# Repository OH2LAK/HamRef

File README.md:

# HamREF

A small GNSS-disciplined 10 MHz frequency reference and precision time server for the amateur radio shack — built around the u-blox LEA-M8S GNSS module.

> **Status: early architecture / pre-prototype.** Proto-1 schematic and PCB (v0.1) are generated and routed, not yet built or tested; a firmware proof of concept (PIO counter + disciplining loop, host-simulated, not yet run on hardware) is in [`firmware/`](firmware/). This README documents the design as currently planned so the repo has a real starting point; sections below are marked `TODO` where work hasn't started.

<p align="center">
  <br>
  <em>Proto-1 bring-up board (v0.1): 4-layer, 100 × 80 mm (fits the Fischer AKG 105.26 case grooves), 3D view from KiCad. Design files in <a href="hardware/proto-v0.1/"><code>hardware/proto-v0.1/</code></a>.</em>
</p>

The proto-1 board has four coaxial connectors along the rear edge: **SMA** (GNSS antenna input), **BNC REF OUT** (10 MHz from the OCXO), **BNC 1PPS OUT** and **BNC AUX OUT**. AUX OUT outputs a programmable frequency (3.3 V CMOS) generated by the Si5351C synthesizer, which is clocked from the OCXO, so it is locked to the same reference as the 10 MHz output.

## What this is

HamREF provides two things a well-equipped station needs and usually has to buy separately:

- A **10 MHz reference output** (BNC, 50 Ω) to lock transceivers, synthesizers, and test equipment, plus a **programmable AUX output** for other frequencies (e.g. 25 MHz, 27 MHz for satellite LNBs, 40 MHz for a Pluto SDR, or an arbitrary frequency).
- A **1 PPS timing output** which can be used to lock and synck devices to the world-standard one pulse per second.
- A **precision time source for the shack computer**, disciplined by GNSS, accurate enough for FT8 and other digital modes.

Status (GNSS lock, satellite count, PPS accuracy, OCXO discipline state) is shown on a small monochrome OLED plus two multicolor status LEDs (GPSDO / NTP) on the front panel — color and blink/steady pattern indicate different states. A front-panel rotary encoder drives the menu; full parameter configuration is also available over USB (see [Enclosure](#enclosure) below).

## Why not just use the GNSS module's own 10 MHz output?

The LEA-M8S can output a configurable timepulse from 0.25 Hz to 10 MHz directly, but that signal is a digitally synthesized pulse train (derived from the module's internal TCXO + fractional-N synthesizer), not a clean analog oscillator. At 10 MHz its jitter (the module's spec is 30 ns RMS / 60 ns 99% at 1 Hz) is significant relative to the 100 ns period, it can show small phase steps at each second boundary, and it provides no holdover if GNSS lock is lost.

HamREF instead uses the classic GPSDO approach: the LEA-M8S's single TIMEPULSE output is configured as **1PPS**, and that one pulse-per-second reference is used by the MCU to discipline a separate free-running OCXO via a DAC-driven EFC loop with a long time constant. The 10 MHz output comes from the OCXO itself — far lower phase noise, plus holdover if satellite lock drops. The same 1PPS/NMEA data feeds the time service to the host computer.

Full rationale and the architecture decision log: [`docs/architecture-and-plan.md`](docs/architecture-and-plan.md) (in Finnish).

## Enclosure

**Fischer Elektronik AKG 105.26** (part AKG1052680ME) — an extruded aluminum mini case for 100 mm eurocards, 105 × 100.3 × 26 mm, natural anodized, with integrated cooling-fin channels. Front and rear panels are separate 2 mm cover plates.

The 26 mm case height (≈22 mm usable panel height) ruled out the originally planned 240x240 color TFT. An EC11-class rotary encoder does fit, though (body ≈11.7×12–13×4.5–8.5 mm, ø7 mm panel bushing — verified against the Farnell EC11 datasheet), so the front panel keeps a physical control after all:

| Panel | Contents |
|---|---|
| Front | 0.91" 128x32 OLED (status), 2 multicolor LEDs (GPSDO, NTP), rotary encoder (menu/control) |
| Rear | SMA (GNSS antenna), BNC (1PPS OUT), BNC (REF OUT 10 MHz), BNC (AUX OUT, programmable), USB-C (host + 5V power) |

The 22 mm limit also constrains component height on the PCB (OCXO included) — still an open item, see the architecture doc.

## Architecture overview

<p align="center">
  <br>
  <em>Block diagram (editable source: <a href="docs/images/HamREF-architecture.svg"><code>HamREF-architecture.svg</code></a>).</em>
</p>

The GNSS module's 1PPS (TIMEPULSE) disciplines the OCXO through the MCU: the RP2350 measures the 10 MHz against the PPS with PIO and steers the EFC through the DAC. REF OUT (10 MHz) comes from the OCXO itself, 1PPS OUT from the GNSS TIMEPULSE, and AUX OUT is a programmable output (Si5351C clocked from the OCXO).

**What is the USB-C port, in plain words?** It is a normal USB-C connector (USB 2.0 only, no Power Delivery, so always 5 V) wired straight to the RP2350's own USB controller. One cable does two jobs: it powers the whole device and it carries data. The data side is a **virtual serial port over USB** (class CDC-ACM): the computer sees an ordinary serial port (`COMx` on Windows, `/dev/ttyACM0` on Linux, `/dev/cu.usbmodem…` on macOS) and needs no special driver. Over that port the device sends the GNSS text sentences and PPS timing data to a small helper program on the computer, which feeds chrony; the computer can also send configuration commands back.

| Acronym | Meaning |
|---|---|
| GNSS | Global Navigation Satellite System: GPS, Galileo, GLONASS, BeiDou |
| 1PPS / PPS | One Pulse Per Second: a pulse aligned to the start of each UTC second |
| TIMEPULSE | u-blox name for the LEA-M8S's programmable timing-pulse output (here set to 1PPS) |
| UART | Universal Asynchronous Receiver/Transmitter: the simple serial link between LEA-M8S and RP2350 |
| NMEA | Text sentences (`$GPGGA`, `$GPRMC` …) in which GNSS receivers report time, position and satellites |
| UBX | u-blox's own binary protocol, used to configure the LEA-M8S |
| USB VBUS | The 5 V power line of a USB cable |
| CDC-ACM | USB Communications Device Class, Abstract Control Model: the standard way to make a USB device look like a serial port |
| PD | USB Power Delivery: negotiation of voltages above 5 V (not used here) |
| I2C | Two-wire bus used for the OLED, the DAC and the Si5351C |
| GPIO | General-purpose input/output pin (drives the status LEDs, reads the encoder) |
| PIO | Programmable I/O: the RP2350's small hardware state machines that count the 10 MHz and timestamp the PPS without CPU jitter |
| Si5351C | Silicon Labs programmable clock generator (I2C); makes the AUX OUT frequency from the OCXO reference |
| OCXO | Oven-Controlled Crystal Oscillator: a crystal kept at constant temperature, the source of the 10 MHz |
| EFC | Electronic Frequency Control: the analog voltage input that fine-tunes the OCXO's frequency |
| DAC | Digital-to-Analog Converter: turns the MCU's number into the EFC voltage |
| SHM | Shared Memory: one of chrony's reference-clock interfaces, where the host helper hands over the timestamps |
| chrony | The time-sync daemon on Linux/macOS that disciplines the computer's clock (an NTP implementation) |
| NTP | Network Time Protocol |

Key hardware decisions so far:

| Item | Decision | Notes |
|---|---|---|
| GNSS module | u-blox LEA-M8S | Fixed — parts already on hand. Footprint and pinout are shared with LEA-M8T. |
| Antenna | Active, external | Antenna supervisor + R_BIAS per u-blox HIM. |
| MCU | RP2350A on a ready-made Raspberry Pi Pico 2 board | Ready-made board keeps HamREF easy to build as a kit. PIO blocks give deterministic 10 MHz counting and 1PPS timestamping without WiFi interrupt jitter; native USB (TinyUSB); UF2 firmware updates. No WiFi in v1. Raspberry Pi Pico 2 (micro-USB) remains a fallback. |
| Oscillator | 5 V OCXO, analog EFC (CTI OSC5A2B02 selected for the prototype) | e.g. Trimble 65256 / IsoTemp 143-141 / CTI OC5SVC25 / Bliley NV47M1008 class part — physical height inside the 22 mm case is still open, see architecture doc. |
| Enclosure | Fischer Elektronik AKG 105.26 (AKG1052680ME) | 105 × 100.3 × 26 mm extruded aluminum, 100 mm eurocard. |
| Display | 0.91" 128x32 mono OLED, I2C | SSD1306-class, 38 × 12 mm PCB (active area 22.4 × 5.6 mm) — fits the 22 mm panel height with margin; 0.96" 128x64 modules do not. |
| Front panel | OLED + 2 multicolor LEDs (GPSDO, NTP) + rotary encoder | EC11-class encoder confirmed to fit the 22 mm panel height. LED color/blink pattern encodes state (firmware TBD). |
| Rear panel | SMA (GNSS antenna), BNC (1PPS OUT), BNC (REF OUT 10 MHz), BNC (AUX OUT, programmable), USB-C (host + 5V power) | All connectors on the back; layout across the 105 mm width still to be confirmed at PCB stage. |
| Power + host link | USB-C | Powers the device (5V); CDC-ACM carries PPS/NMEA to a host-side helper feeding chrony (SHM/PPS refclock), and doubles as the configuration interface alongside the encoder/OLED menu. |

See the architecture doc for the full reasoning, open questions, and the phased project plan.

## Status / roadmap

- [x] Requirements and architecture defined
- [x] Enclosure selected (Fischer AKG 105.26) and display/panel layout locked to it
- [x] MCU selected (RP2350 / Pico 2)
- [ ] Proto-PCB v0.1 (bring-up board, see architecture doc)
- [ ] Breadboard proof of concept (PIO PPS capture + frequency counting, disciplining loop, USB time delivery)
- [ ] KiCad schematic
- [ ] PCB layout
- [ ] Enclosure machining (panel cutouts)
- [x] Firmware proof of concept (PIO gate counter, disciplining loop, host simulation) - see [`firmware/`](firmware/)
- [ ] Firmware on real hardware (calibration, OLED/menu, GNSS configuration, host helper)
- [ ] Calibration and verification against a reference

## Repository structure

```
hardware/proto-v0.1/   KiCad project (schematic, PCB) for the proto-1 board
hardware/tools/        Python scripts that generate the schematic/PCB
firmware/              RP2350 firmware (Pico SDK) and host simulation
docs/                  Architecture notes, hardware plans, images
```

## Building it yourself

Firmware: see [`firmware/README.md`](firmware/README.md) (Pico SDK, CMake, UF2). The disciplining loop can be tried without hardware with the host simulation described there. Hardware: open `hardware/proto-v0.1/` in KiCad; the pre-order checklist is in [`docs/hardware/board-finishing-checklist.md`](docs/hardware/board-finishing-checklist.md). A bill of materials and bring-up guide will follow once the board is built.

## Hardware reference documents

Design decisions are based on:
- u-blox LEA-M8S Data Sheet (UBX-16010205)
- u-blox LEA-M8S/M8T Hardware Integration Manual (UBX-15030060)
- Fischer Elektronik AKG1052680ME data sheet (enclosure)
- Raspberry Pi RP2350 datasheet and Waveshare RP2350-Plus schematic / STEP model (`docs/datasheets/`)

## License

Not chosen yet (candidates: CERN-OHL-S for hardware, MIT or GPL for firmware, CC BY-SA for docs). Until a license is added, all rights are reserved.

## Authors

Erik, OH2LAK
Others will be too, when I find them and convince them this is a good project :)

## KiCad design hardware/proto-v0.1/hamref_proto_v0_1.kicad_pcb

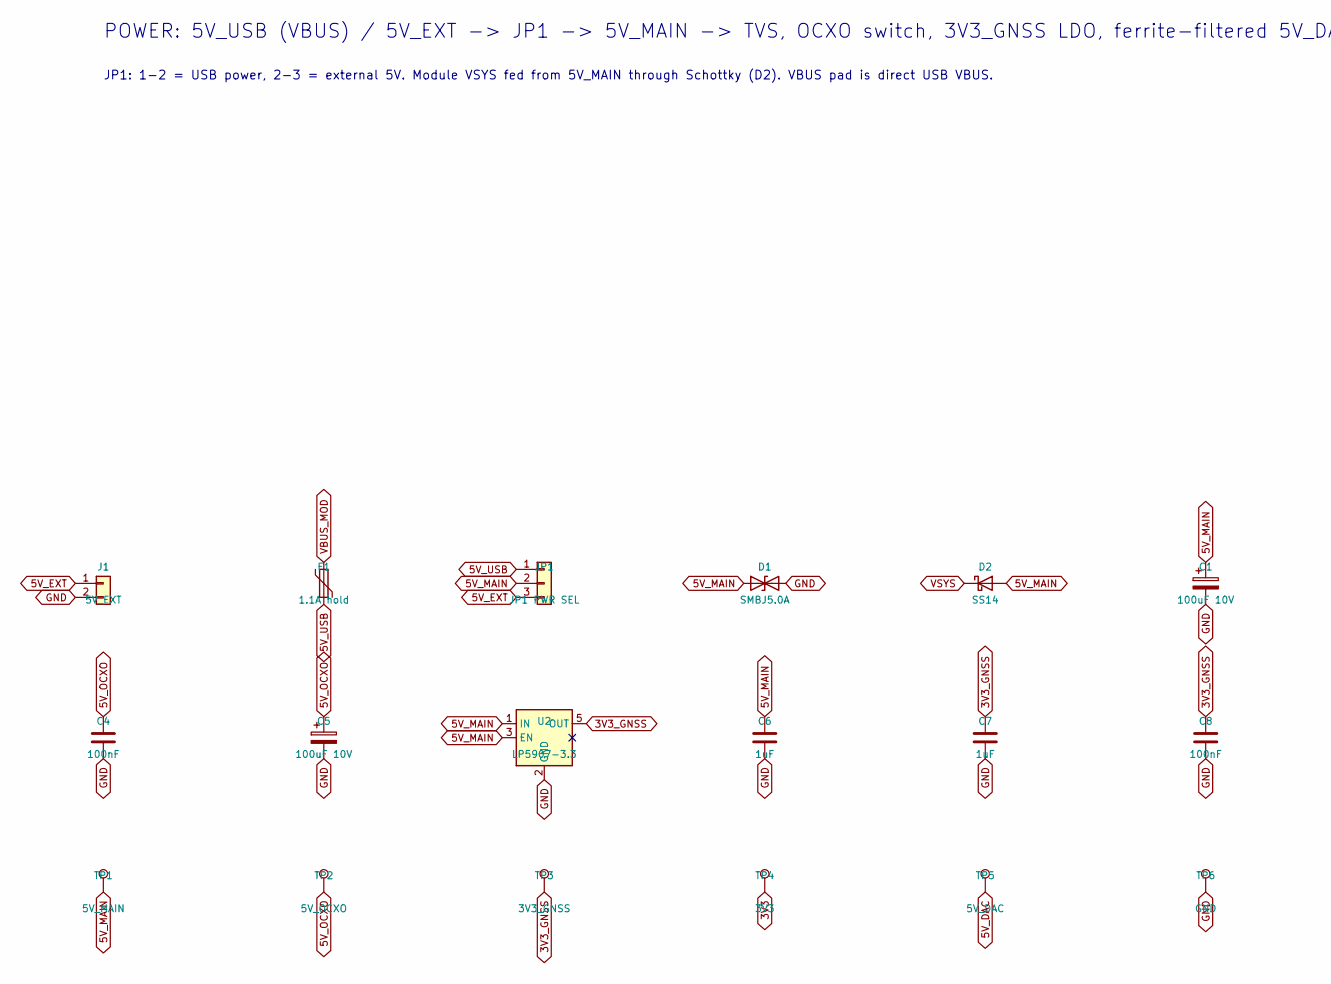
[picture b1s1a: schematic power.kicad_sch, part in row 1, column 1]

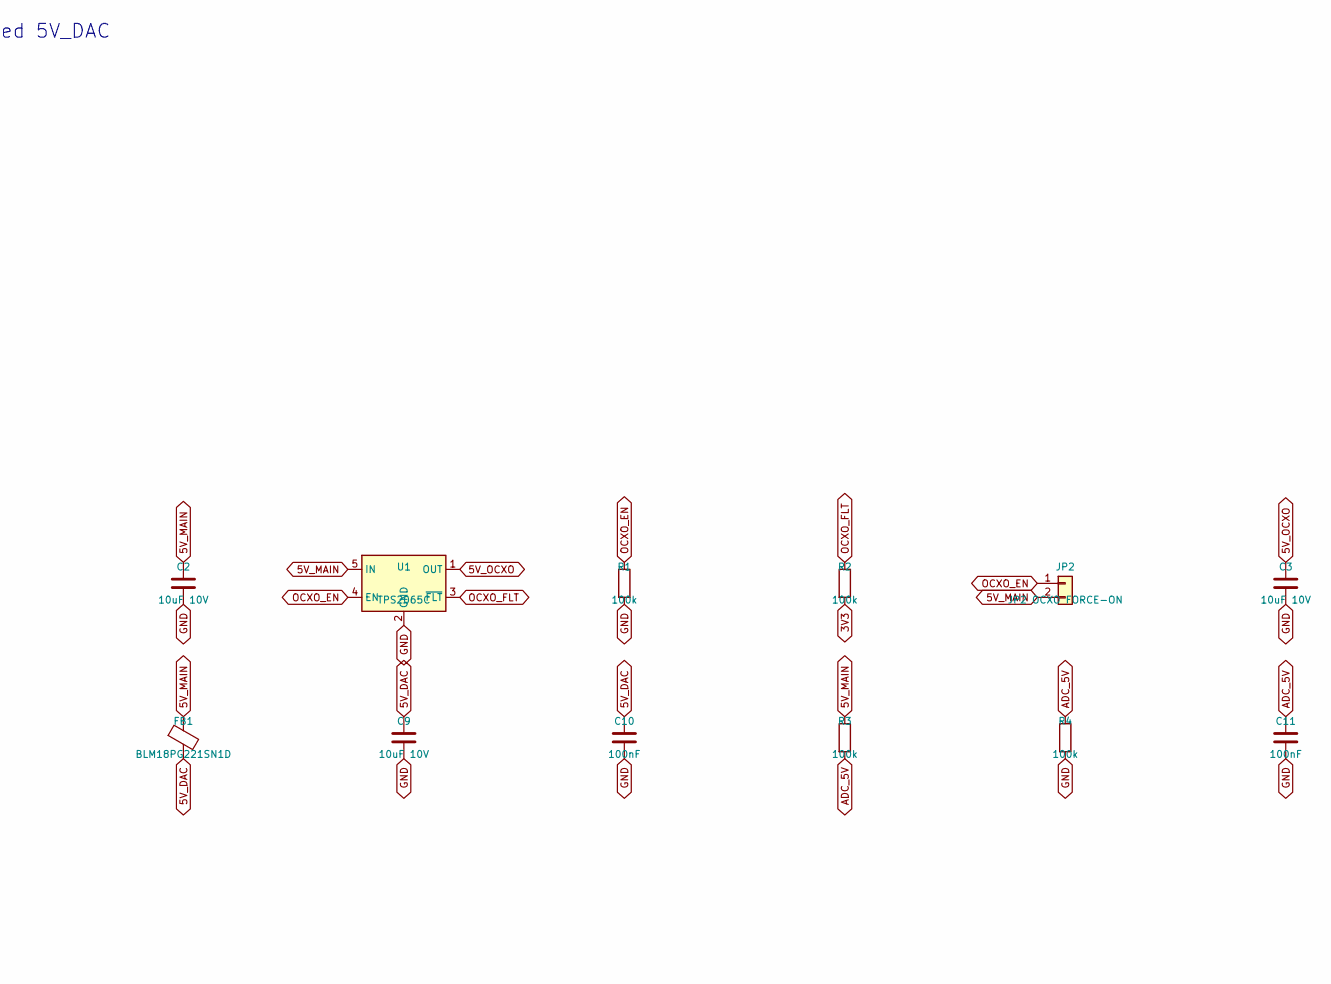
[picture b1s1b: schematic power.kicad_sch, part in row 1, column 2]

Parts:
C1, C5: 100uF 10V; CP_Radial_D6.3mm_P2.50mm
C2, C3, C9: 10uF 10V; C_0805_2012Metric
C4, C8, C10, C11: 100nF; C_0402_1005Metric
C6, C7: 1uF; C_0603_1608Metric
D1: SMBJ5.0A; D_SMB; MPN SMBJ5.0A
D2: SS14; D_SMA; MPN SS14
F1: 1.1A hold; Fuse_1812_4532Metric; MPN MF-MSMF110/16X-2
FB1: BLM18PG221SN1D; L_0603_1608Metric; MPN BLM18PG221SN1D
J1: 5V_EXT; PinHeader_1x02_P2.54mm_Vertical
JP1: JP1 PWR SEL; PinHeader_1x03_P2.54mm_Vertical
JP2: JP2 OCXO FORCE-ON; PinHeader_1x02_P2.54mm_Vertical
R1, R2, R3, R4: 100k; R_0402_1005Metric
TP1: 5V_MAIN; TestPoint_Pad_D1.5mm
TP2: 5V_OCXO; TestPoint_Pad_D1.5mm
TP3: 3V3_GNSS; TestPoint_Pad_D1.5mm
TP4: 3V3; TestPoint_Pad_D1.5mm
TP5: 5V_DAC; TestPoint_Pad_D1.5mm
TP6: GND; TestPoint_Pad_D1.5mm
U1: TPS2065C; SOT-23-5; MPN TPS2065CDBVR
U2: LP5907-3.3; SOT-23-5; MPN LP5907MFX-3.3/NOPB

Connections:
3V3: R2.2, TP4.1; also elsewhere on the board
3V3_GNSS: C7.1, C8.1, TP3.1, U2.5 (OUT); also elsewhere on the board
5V_DAC: C9.1, C10.1, FB1.2, TP5.1; also elsewhere on the board
5V_EXT: J1.1, JP1.3
5V_MAIN: C1.1, C2.1, C6.1, D1.1 (A1), D2.2 (A), FB1.1, JP1.2, JP2.2, R3.1, TP1.1, U1.5 (IN), U2.1 (IN), U2.3 (EN); also elsewhere on the board
5V_OCXO: C3.1, C4.1, C5.1, TP2.1, U1.1 (OUT); also elsewhere on the board
5V_USB: F1.2, JP1.1
ADC_5V: C11.1, R3.2, R4.1; also elsewhere on the board
GND: C1.2, C2.2, C3.2, C4.2, C5.2, C6.2, C7.2, C8.2, C9.2, C10.2, C11.2, D1.2 (A2), J1.2, R1.2, R4.2, TP6.1, U1.2 (GND), U2.2 (GND); also elsewhere on the board
OCXO_EN: JP2.1, R1.1, U1.4 (EN); also elsewhere on the board
OCXO_FLT: R2.1, U1.3 (~FLT)
VBUS_MOD: F1.1; also elsewhere on the board
VSYS: D2.1 (K); also elsewhere on the board

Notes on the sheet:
POWER: 5V_USB (VBUS) / 5V_EXT -> JP1 -> 5V_MAIN -> TVS, OCXO switch, 3V3_GNSS LDO, ferrite-filtered 5V_DAC
JP1: 1-2 = USB power, 2-3 = external 5V. Module VSYS fed from 5V_MAIN through Schottky (D2). VBUS pad is direct USB VBUS.

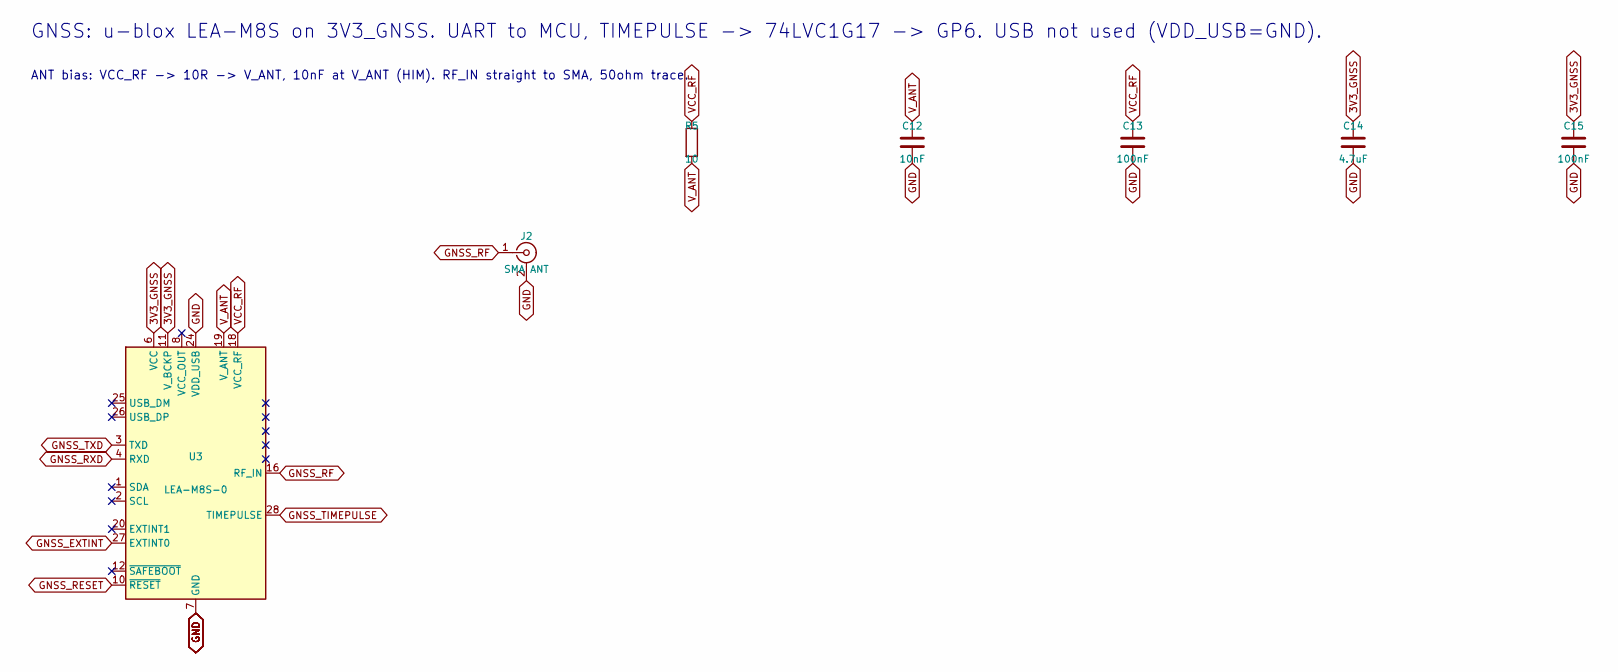
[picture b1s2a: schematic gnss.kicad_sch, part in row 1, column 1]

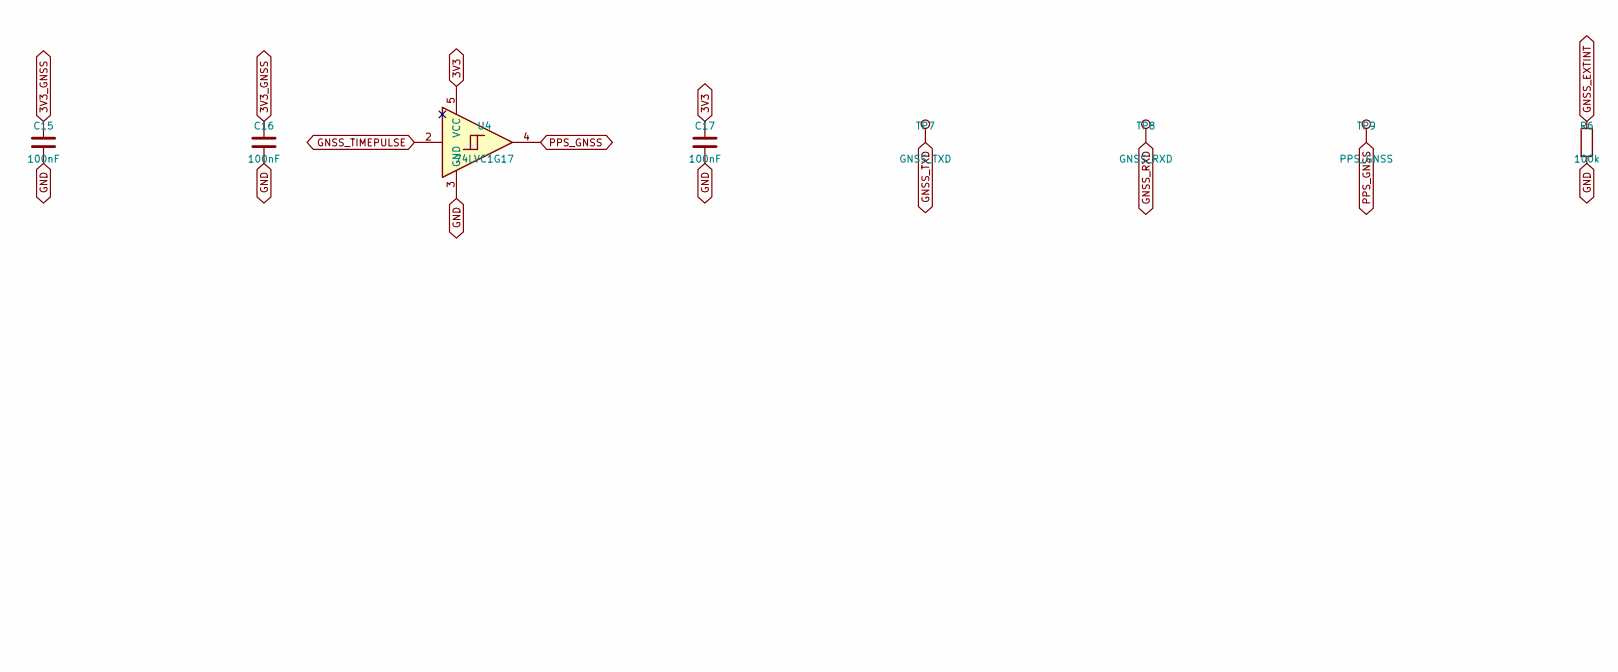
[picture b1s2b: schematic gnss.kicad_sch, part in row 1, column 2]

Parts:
C12: 10nF; C_0402_1005Metric
C13, C15, C16, C17: 100nF; C_0402_1005Metric
C14: 4.7uF; C_0603_1608Metric
J2: SMA ANT; SMA_Amphenol_901-143_Horizontal; MPN 901-143
R5: 10; R_0402_1005Metric
R6: 100k; R_0402_1005Metric
TP7: GNSS_TXD; TestPoint_Pad_D1.5mm
TP8: GNSS_RXD; TestPoint_Pad_D1.5mm
TP9: PPS_GNSS; TestPoint_Pad_D1.5mm
U3: LEA-M8S-0; ublox_LEA; MPN LEA-M8S-0-10
U4: 74LVC1G17; SOT-23-5; MPN SN74LVC1G17DBVR

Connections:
3V3: C17.1, U4.5 (VCC); also elsewhere on the board
3V3_GNSS: C14.1, C15.1, C16.1, U3.6 (VCC), U3.11 (V_BCKP); also elsewhere on the board
GND: C12.2, C13.2, C14.2, C15.2, C16.2, C17.2, J2.2 (Ext), R6.2, U3.7 (GND), U3.13 (GND), U3.14 (GND), U3.15 (GND), U3.17 (GND), U3.24 (VDD_USB), U4.3 (GND); also elsewhere on the board
GNSS_EXTINT: R6.1, U3.27 (EXTINT0); also elsewhere on the board
GNSS_RESET: U3.10 (~RESET); also elsewhere on the board
GNSS_RF: J2.1 (In), U3.16 (RF_IN)
GNSS_RXD: TP8.1, U3.4 (RXD); also elsewhere on the board
GNSS_TIMEPULSE: U3.28 (TIMEPULSE), U4.2
GNSS_TXD: TP7.1, U3.3 (TXD); also elsewhere on the board
PPS_GNSS: TP9.1, U4.4; also elsewhere on the board
VCC_RF: C13.1, R5.1, U3.18 (VCC_RF)
V_ANT: C12.1, R5.2, U3.19 (V_ANT)

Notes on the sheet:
GNSS: u-blox LEA-M8S on 3V3_GNSS. UART to MCU, TIMEPULSE -> 74LVC1G17 -> GP6. USB not used (VDD_USB=GND).
ANT bias: VCC_RF -> 10R -> V_ANT, 10nF at V_ANT (HIM). RF_IN straight to SMA, 50ohm trace.

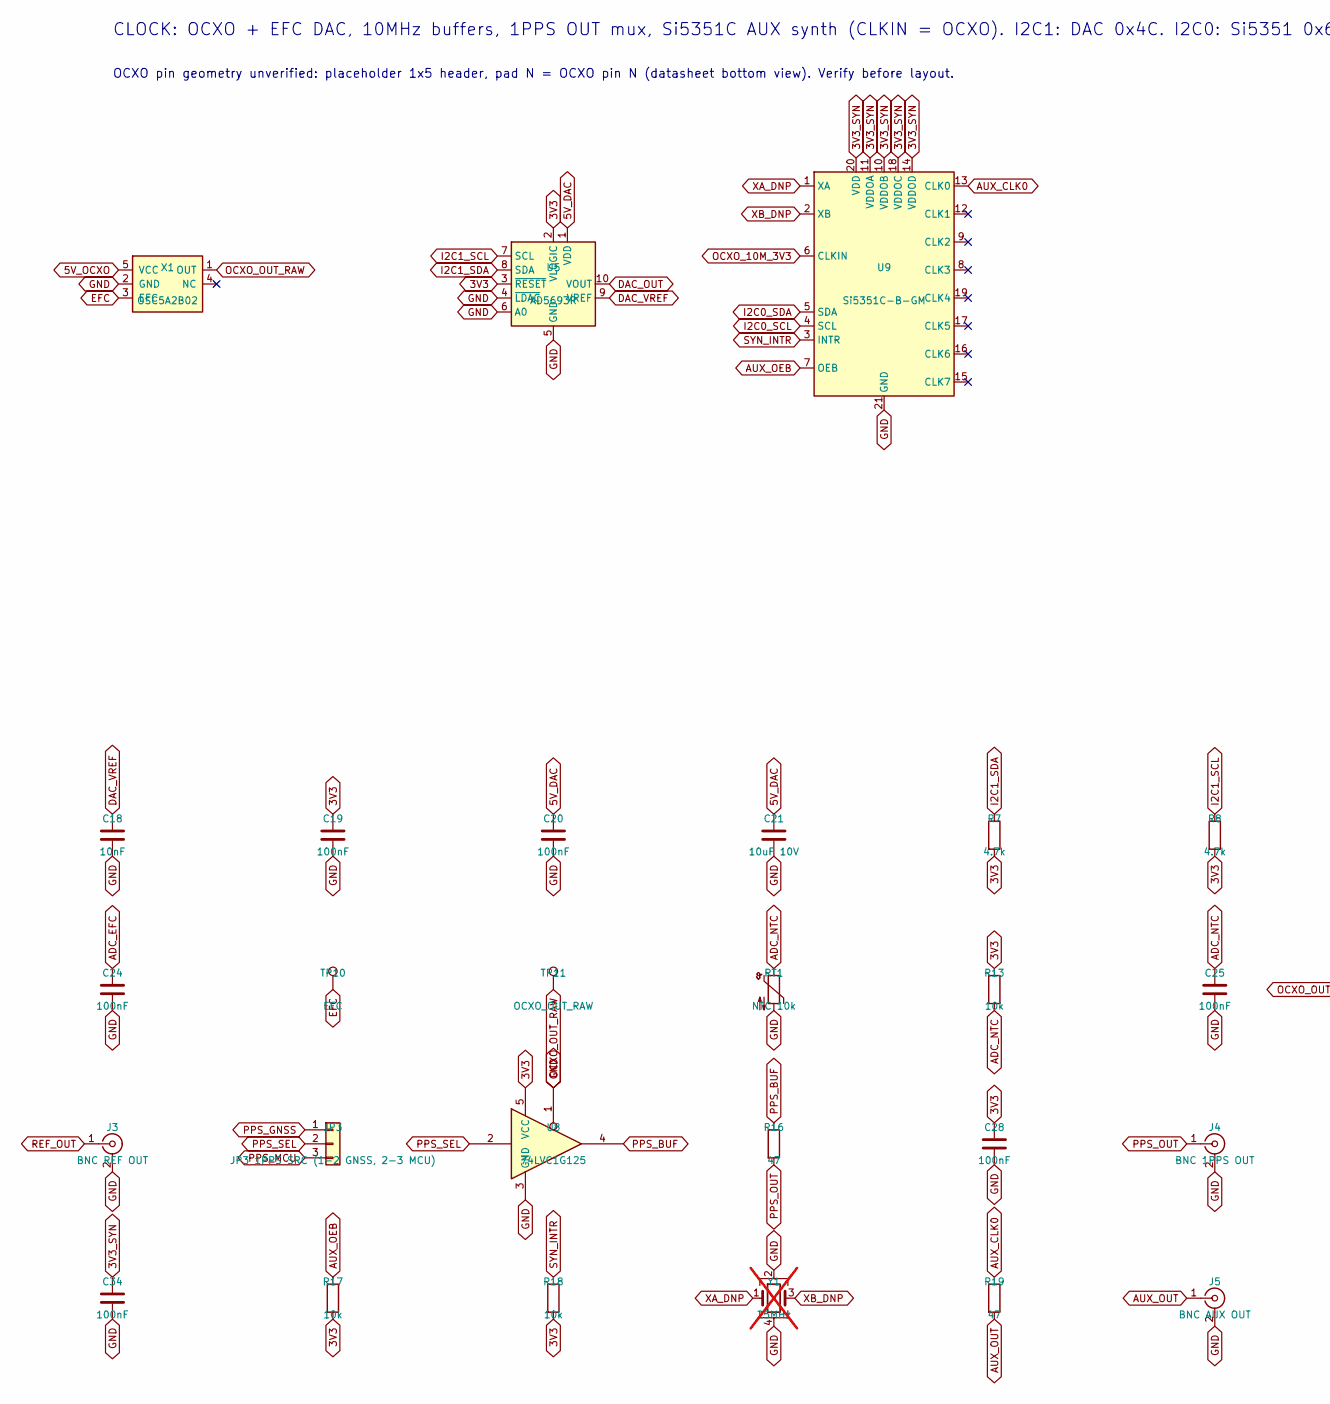
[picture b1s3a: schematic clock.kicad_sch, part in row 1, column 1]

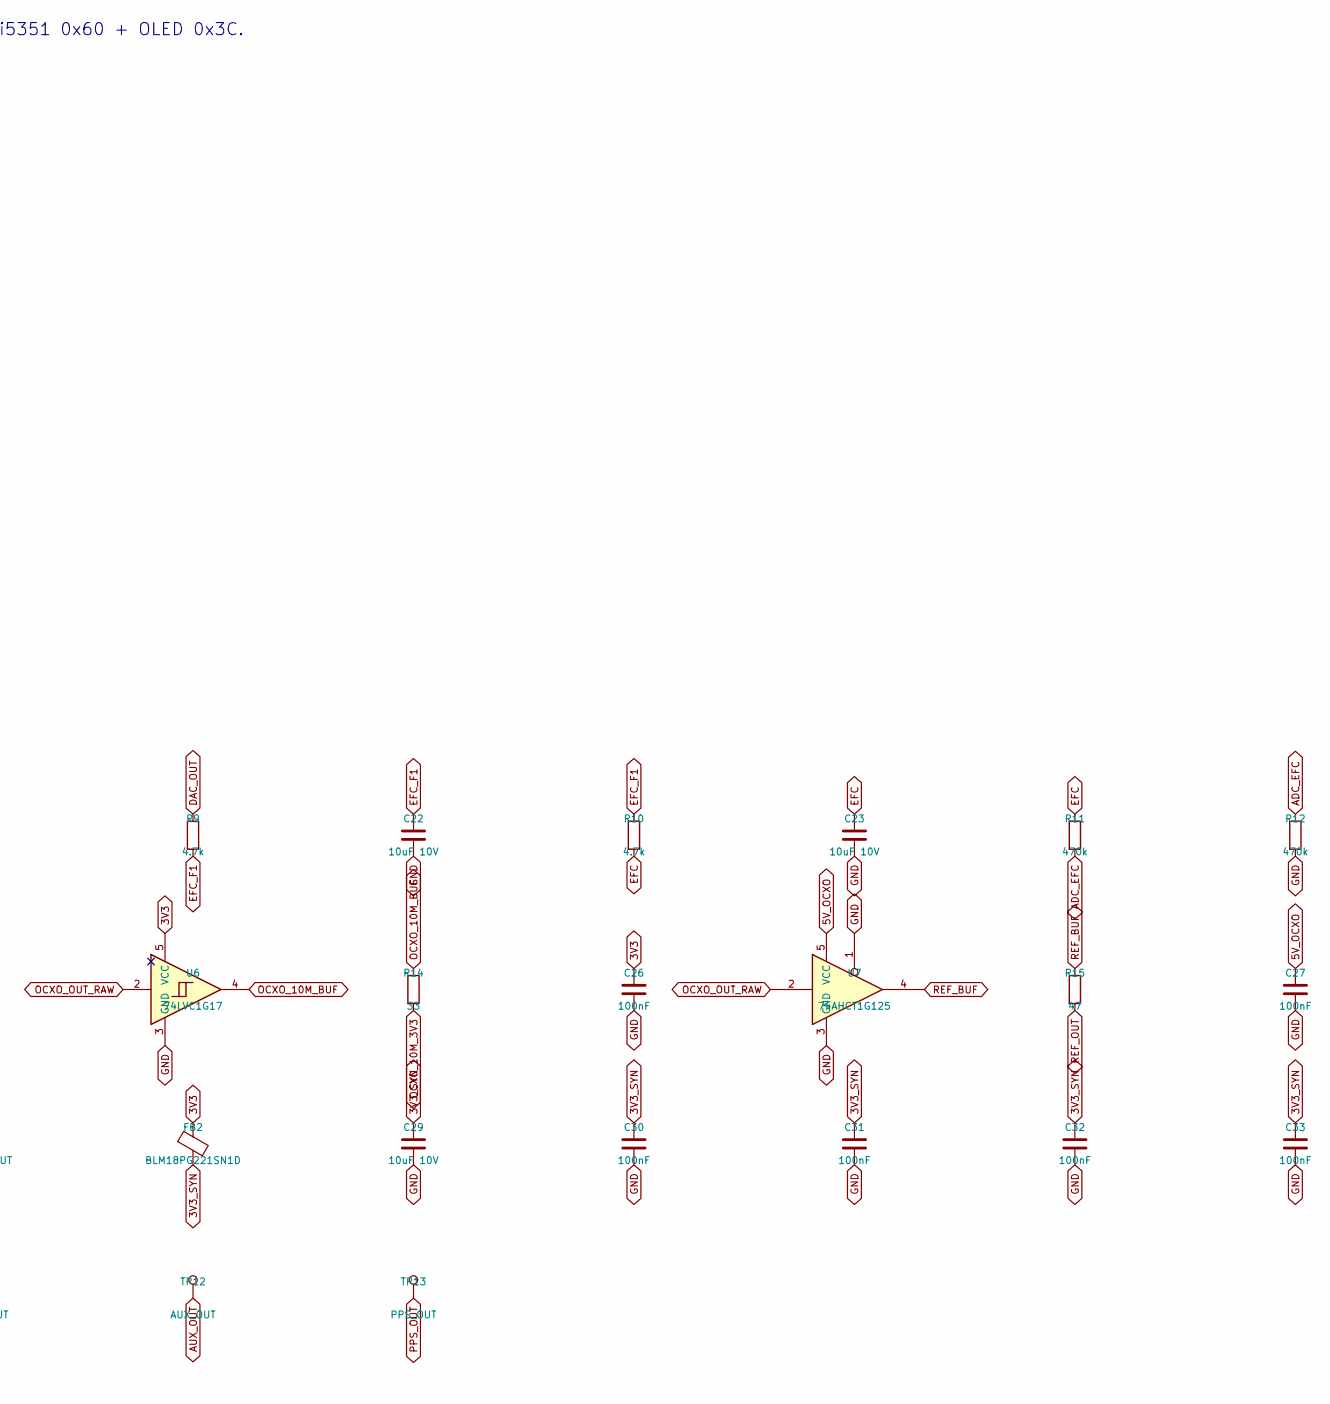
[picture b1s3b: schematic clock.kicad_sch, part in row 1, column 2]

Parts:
C18: 10nF; C_0402_1005Metric
C19, C20, C24, C25, C26, C27, C28, C30, C31, C32, C33, C34: 100nF; C_0402_1005Metric
C21, C22, C23, C29: 10uF 10V; C_0805_2012Metric
FB2: BLM18PG221SN1D; L_0603_1608Metric; MPN BLM18PG221SN1D
J3: BNC REF OUT; BNC_TEConnectivity_1478035_Horizontal; MPN 1-1478035-0
J4: BNC 1PPS OUT; BNC_TEConnectivity_1478035_Horizontal; MPN 1-1478035-0
J5: BNC AUX OUT; BNC_TEConnectivity_1478035_Horizontal; MPN 1-1478035-0
JP3: JP3 1PPS SRC (1-2 GNSS, 2-3 MCU); PinHeader_1x03_P2.54mm_Vertical
R7, R8, R9, R10: 4.7k; R_0402_1005Metric
R11, R12: 470k; R_0402_1005Metric
R13, R17, R18: 10k; R_0402_1005Metric
R14: 33; R_0402_1005Metric
R15, R16, R19: 47; R_0402_1005Metric
RT1: NTC 10k; R_0603_1608Metric; MPN NCP18XH103F03RB
TP10: EFC; TestPoint_Pad_D1.5mm
TP11: OCXO_OUT_RAW; TestPoint_Pad_D1.5mm
TP12: AUX_OUT; TestPoint_Pad_D1.5mm
TP13: PPS_OUT; TestPoint_Pad_D1.5mm
U5: AD5693R; MSOP-10_3x3mm_P0.5mm; MPN AD5693RBRMZ
U6: 74LVC1G17; SOT-23-5; MPN SN74LVC1G17DBVR
U7: 74AHCT1G125; SOT-23-5; MPN SN74AHCT1G125DBVR
U8: 74LVC1G125; SOT-23-5; MPN SN74LVC1G125DBVR
U9: Si5351C-B-GM; QFN-20-1EP_4x4mm_P0.5mm_EP2.6x2.6mm; MPN SI5351C-B-GM
X1: OSC5A2B02; OCXO_OSC5A2B02_EST; MPN OSC5A2B02
Y1: 25MHz; Crystal_SMD_3225-4Pin_3.2x2.5mm; not fitted

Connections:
3V3: C19.1, C26.1, C28.1, FB2.1, R7.2, R8.2, R13.1, R17.2, R18.2, U5.2 (VLOGIC), U5.3 (~RESET), U6.5 (VCC), U8.5 (VCC); also elsewhere on the board
3V3_SYN: C29.1, C30.1, C31.1, C32.1, C33.1, C34.1, FB2.2, U9.10 (VDDOB), U9.11 (VDDOA), U9.14 (VDDOD), U9.18 (VDDOC), U9.20 (VDD)
5V_DAC: C20.1, C21.1, U5.1 (VDD); also elsewhere on the board
5V_OCXO: C27.1, U7.5 (VCC), X1.5 (VCC); also elsewhere on the board
ADC_EFC: C24.1, R11.2, R12.1; also elsewhere on the board
ADC_NTC: C25.1, R13.2, RT1.1; also elsewhere on the board
AUX_CLK0: R19.1, U9.13 (CLK0)
AUX_OEB: R17.1, U9.7 (OEB); also elsewhere on the board
AUX_OUT: J5.1 (In), R19.2, TP12.1
DAC_OUT: R9.1, U5.10 (VOUT)
DAC_VREF: C18.1, U5.9 (VREF)
EFC: C23.1, R10.2, R11.1, TP10.1, X1.3 (EFC)
EFC_F1: C22.1, R9.2, R10.1
GND: C18.2, C19.2, C20.2, C21.2, C22.2, C23.2, C24.2, C25.2, C26.2, C27.2, C28.2, C29.2, C30.2, C31.2, C32.2, C33.2, C34.2, J3.2 (Ext), J4.2 (Ext), J5.2 (Ext), R12.2, RT1.2, U5.4 (~LDAC), U5.5 (GND), U5.6 (A0), U6.3 (GND), U7.1, U7.3 (GND), U8.1, U8.3 (GND), U9.21 (GND), X1.2 (GND), Y1.2, Y1.4; also elsewhere on the board
I2C0_SCL: U9.4 (SCL); also elsewhere on the board
I2C0_SDA: U9.5 (SDA); also elsewhere on the board
I2C1_SCL: R8.1, U5.7 (SCL); also elsewhere on the board
I2C1_SDA: R7.1, U5.8 (SDA); also elsewhere on the board
OCXO_10M_3V3: R14.2, U9.6 (CLKIN); also elsewhere on the board
OCXO_10M_BUF: R14.1, U6.4
OCXO_OUT_RAW: TP11.1, U6.2, U7.2, X1.1 (OUT)
PPS_BUF: R16.1, U8.4
PPS_GNSS: JP3.1; also elsewhere on the board
PPS_MCU: JP3.3; also elsewhere on the board
PPS_OUT: J4.1 (In), R16.2, TP13.1
PPS_SEL: JP3.2, U8.2
REF_BUF: R15.1, U7.4
REF_OUT: J3.1 (In), R15.2
SYN_INTR: R18.1, U9.3 (INTR); also elsewhere on the board
XA_DNP: U9.1 (XA), Y1.1
XB_DNP: U9.2 (XB), Y1.3

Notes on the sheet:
CLOCK: OCXO + EFC DAC, 10MHz buffers, 1PPS OUT mux, Si5351C AUX synth (CLKIN = OCXO). I2C1: DAC 0x4C. I2C0: Si5351 0x60 + OLED 0x3C.
OCXO pin geometry unverified: placeholder 1x5 header, pad N = OCXO pin N (datasheet bottom view). Verify before layout.

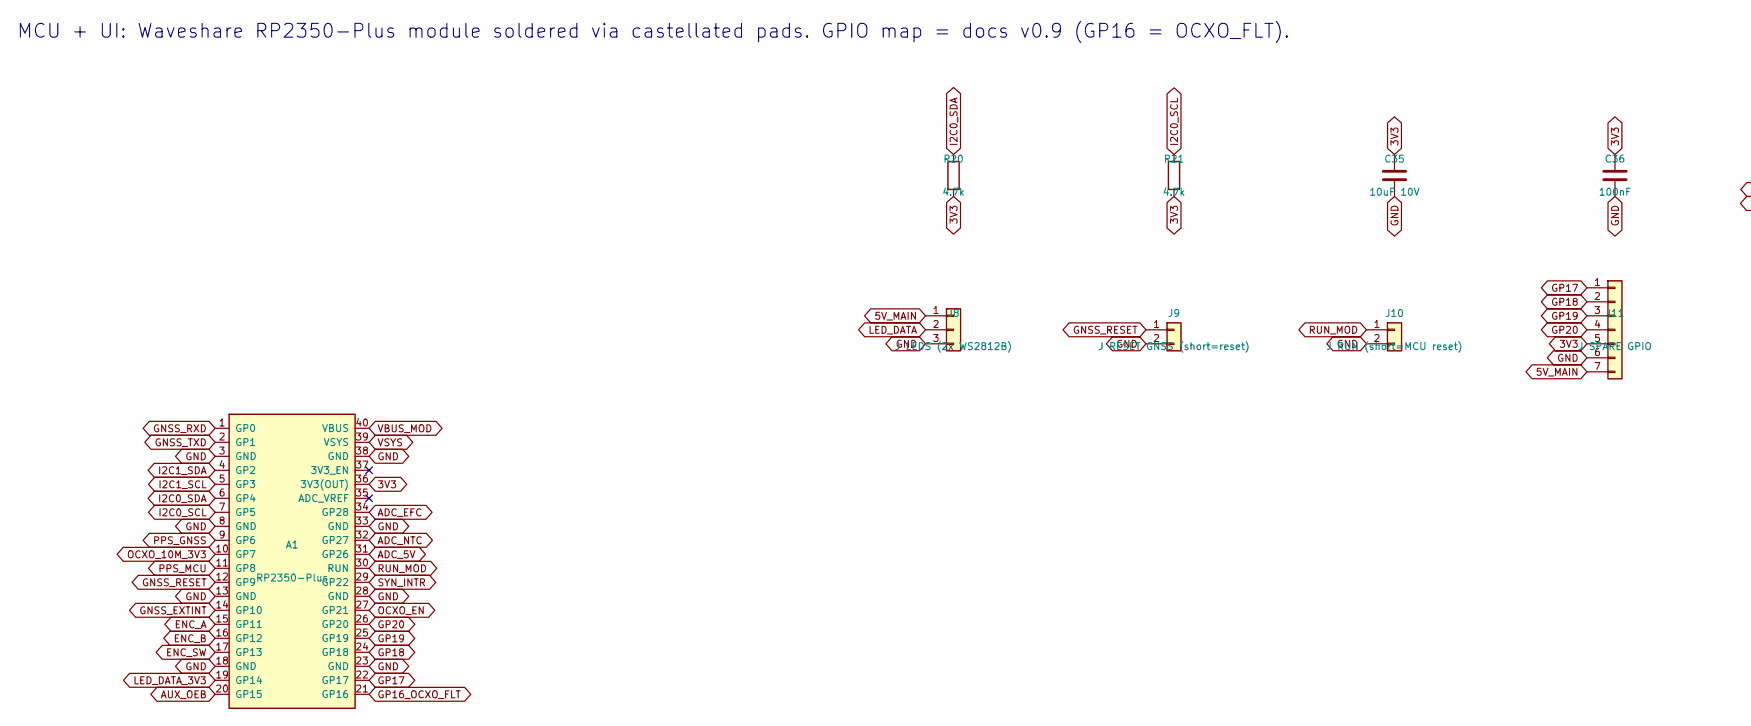
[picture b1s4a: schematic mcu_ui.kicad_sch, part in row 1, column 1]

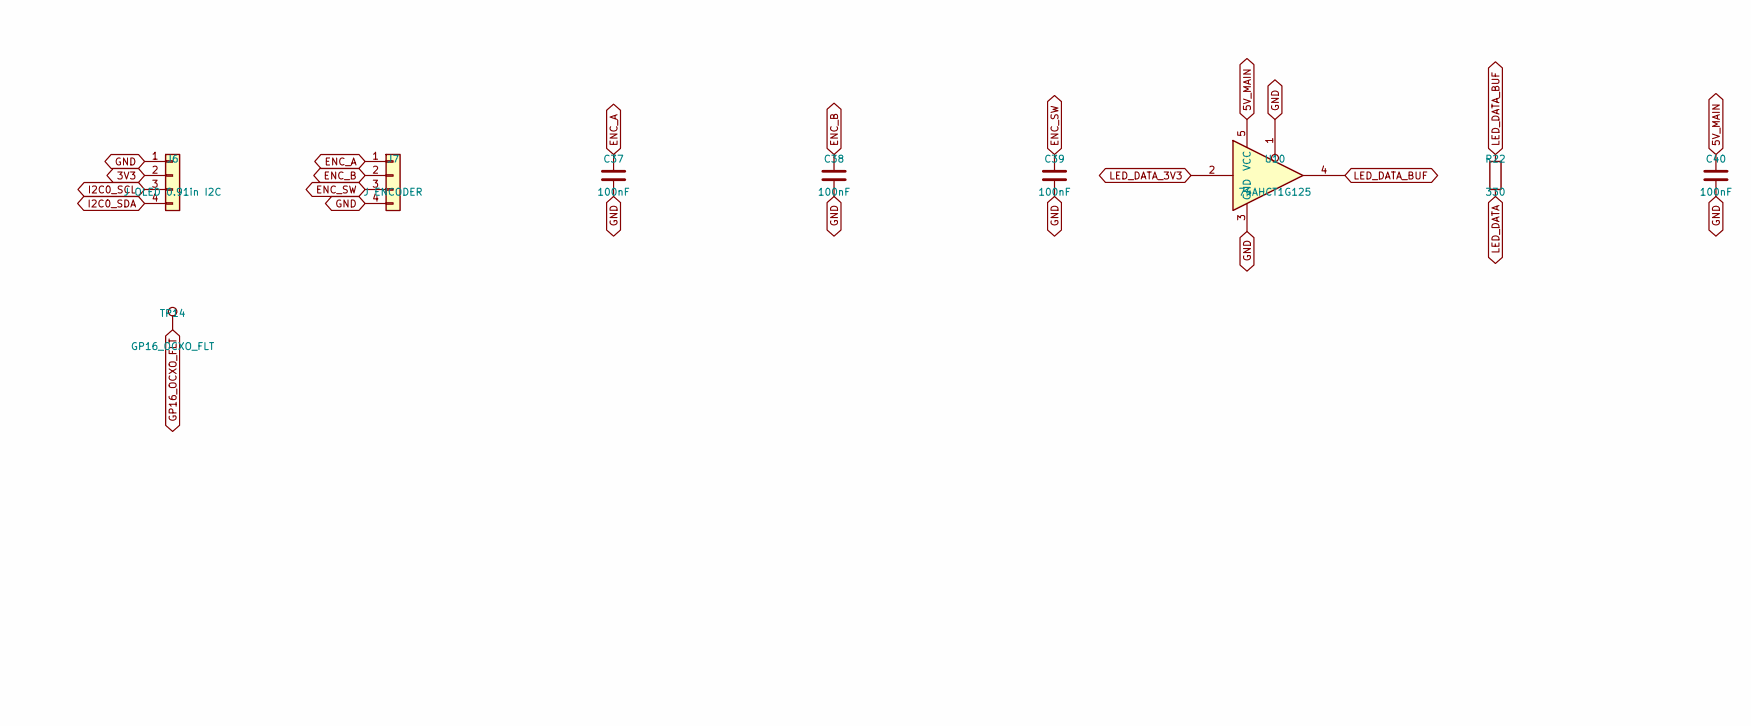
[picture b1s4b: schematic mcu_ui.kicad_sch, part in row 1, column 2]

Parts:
A1: RP2350-Plus; RP2350-Plus_Castellated; MPN RP2350-Plus
C35: 10uF 10V; C_0805_2012Metric
C36, C37, C38, C39, C40: 100nF; C_0402_1005Metric
J6: J OLED 0.91in I2C; PinHeader_1x04_P2.54mm_Vertical
J7: J ENCODER; PinHeader_1x04_P2.54mm_Vertical
J8: J LEDS (2x WS2812B); PinHeader_1x03_P2.54mm_Vertical
J9: J RESET GNSS (short=reset); PinHeader_1x02_P2.54mm_Vertical
J10: J RUN (short=MCU reset); PinHeader_1x02_P2.54mm_Vertical
J11: J SPARE GPIO; PinHeader_1x07_P2.54mm_Vertical
R20, R21: 4.7k; R_0402_1005Metric
R22: 330; R_0402_1005Metric
TP14: GP16_OCXO_FLT; TestPoint_Pad_D1.5mm
U10: 74AHCT1G125; SOT-23-5; MPN SN74AHCT1G125DBVR

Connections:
3V3: A1.36 (3V3(OUT)), C35.1, C36.1, J6.2, J11.5, R20.2, R21.2; also elsewhere on the board
5V_MAIN: C40.1, J8.1, J11.7, U10.5 (VCC); also elsewhere on the board
ADC_5V: A1.31 (GP26); also elsewhere on the board
ADC_EFC: A1.34 (GP28); also elsewhere on the board
ADC_NTC: A1.32 (GP27); also elsewhere on the board
AUX_OEB: A1.20 (GP15); also elsewhere on the board
ENC_A: A1.15 (GP11), C37.1, J7.1
ENC_B: A1.16 (GP12), C38.1, J7.2
ENC_SW: A1.17 (GP13), C39.1, J7.3
GND: A1.3 (GND), A1.8 (GND), A1.13 (GND), A1.18 (GND), A1.23 (GND), A1.28 (GND), A1.33 (GND), A1.38 (GND), C35.2, C36.2, C37.2, C38.2, C39.2, C40.2, J6.1, J7.4, J8.3, J9.2, J10.2, J11.6, U10.1, U10.3 (GND); also elsewhere on the board
GNSS_EXTINT: A1.14 (GP10); also elsewhere on the board
GNSS_RESET: A1.12 (GP9), J9.1; also elsewhere on the board
GNSS_RXD: A1.1 (GP0); also elsewhere on the board
GNSS_TXD: A1.2 (GP1); also elsewhere on the board
GP16_OCXO_FLT: A1.21 (GP16), TP14.1
GP17: A1.22 (GP17), J11.1
GP18: A1.24 (GP18), J11.2
GP19: A1.25 (GP19), J11.3
GP20: A1.26 (GP20), J11.4
I2C0_SCL: A1.7 (GP5), J6.3, R21.1; also elsewhere on the board
I2C0_SDA: A1.6 (GP4), J6.4, R20.1; also elsewhere on the board
I2C1_SCL: A1.5 (GP3); also elsewhere on the board
I2C1_SDA: A1.4 (GP2); also elsewhere on the board
LED_DATA: J8.2, R22.2
LED_DATA_3V3: A1.19 (GP14), U10.2
LED_DATA_BUF: R22.1, U10.4
OCXO_10M_3V3: A1.10 (GP7); also elsewhere on the board
OCXO_EN: A1.27 (GP21); also elsewhere on the board
PPS_GNSS: A1.9 (GP6); also elsewhere on the board
PPS_MCU: A1.11 (GP8); also elsewhere on the board
RUN_MOD: A1.30 (RUN), J10.1
SYN_INTR: A1.29 (GP22); also elsewhere on the board
VBUS_MOD: A1.40 (VBUS); also elsewhere on the board
VSYS: A1.39 (VSYS); also elsewhere on the board

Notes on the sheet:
MCU + UI: Waveshare RP2350-Plus module soldered via castellated pads. GPIO map = docs v0.9 (GP16 = OCXO_FLT).

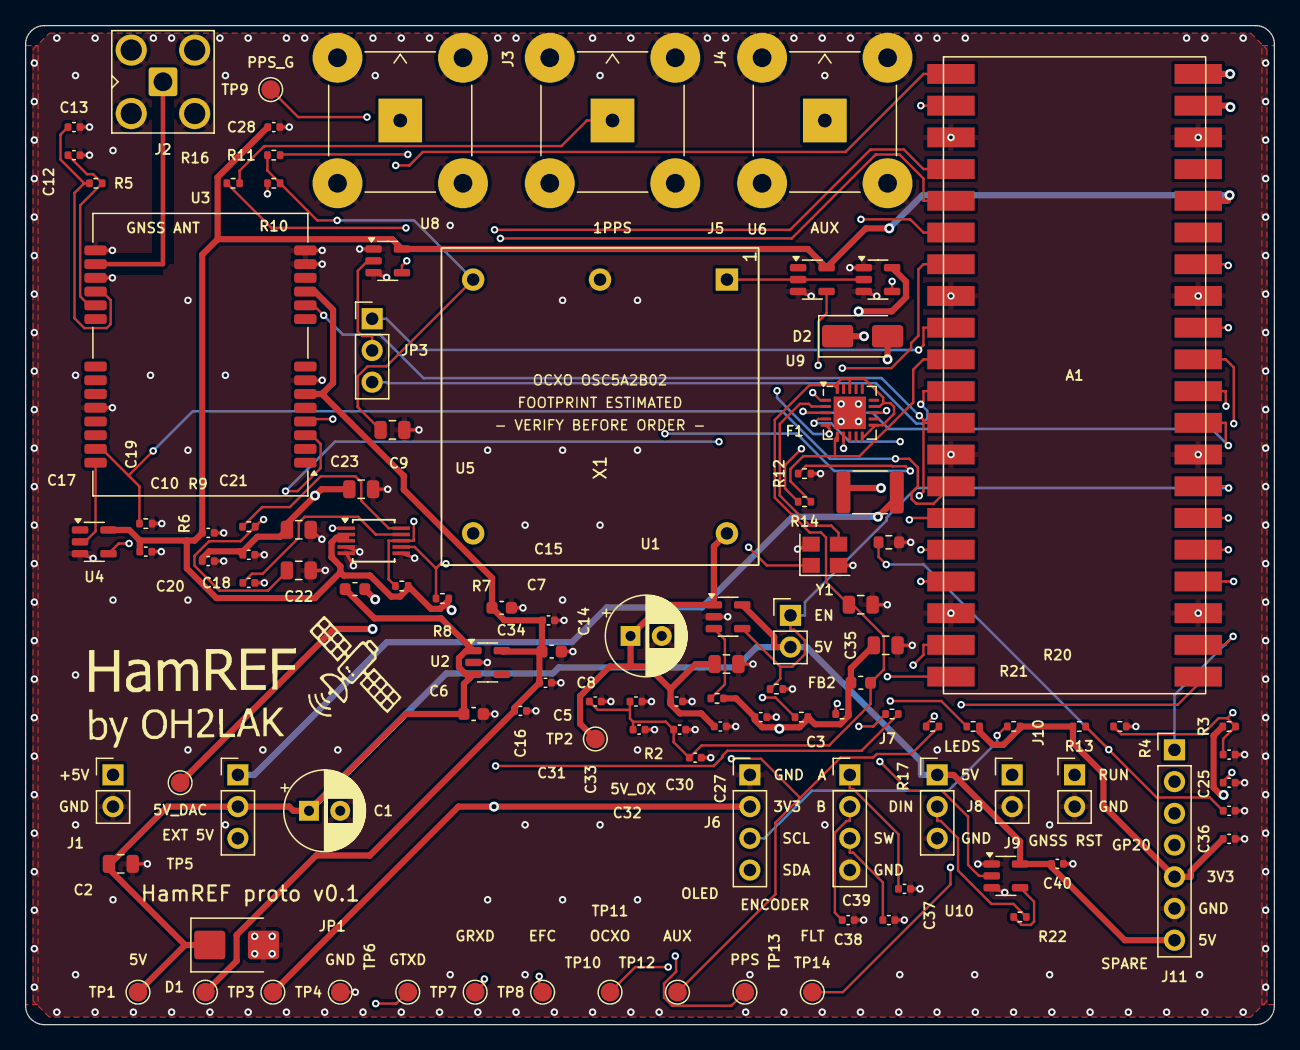
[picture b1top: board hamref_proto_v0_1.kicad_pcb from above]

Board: 4 copper layers, 100.0 x 80.0 mm, 109 parts (0 on the bottom side), 60 nets.

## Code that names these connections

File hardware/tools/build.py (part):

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N.text('GNSS: u-blox LEA-M8S on 3V3_GNSS. UART to MCU, TIMEPULSE -> 74LVC1G17 -> GP6. USB not used (VDD_USB=GND).', 30, 20, 2.5)
N.text('ANT bias: VCC_RF -> 10R -> V_ANT, 10nF at V_ANT (HIM). RF_IN straight to SMA, 50ohm trace.', 30, 28, 1.6)
N.add(ref('U'),'RF_GPS','LEA-M8S','LEA-M8S-0',
  pins={'3':'GNSS_TXD','4':'GNSS_RXD','6':'3V3_GNSS','10':'GNSS_RESET','11':'3V3_GNSS','16':'GNSS_RF','18':'VCC_RF','19':'V_ANT','24':'GND','27':'GNSS_EXTINT','28':'GNSS_TIMEPULSE'},
  nc=('1','2','5','8','9','12','20','21','22','23','25','26'), fp=FP['lea'], xy=(60,100), mpn='LEA-M8S-0-10', mfr='u-blox',
  note='RESET_N: drive low or hi-Z only. SDA/SCL (DDC) unused. USB unused.')
LEA = N.last
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K = S('Clock','clock.kicad_sch', 30, 160)
K.text('CLOCK: OCXO + EFC DAC, 10MHz buffers, 1PPS OUT mux, Si5351C AUX synth (CLKIN = OCXO). I2C1: DAC 0x4C. I2C0: Si5351 0x60 + OLED 0x3C.', 30, 14, 2.2)
K.text('OCXO pin geometry unverified: placeholder 1x5 header, pad N = OCXO pin N (datasheet bottom view). Verify before layout.', 30, 22, 1.6)
K.add(ref('X'),'HamREF','OCXO_OSC5A2B02','OSC5A2B02',pins={'1':'OCXO_OUT_RAW','5':'5V_OCXO','2':'GND','3':'EFC'},nc=('4',),fp=FP['ocxo'],xy=(40,60),mfr='CTI',mpn='OSC5A2B02',note='used units often salvaged: test before fitting')
OCXO = K.last
# DAC
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K.add(ref('J'),'Connector','Conn_Coaxial','BNC 1PPS OUT',{'1':'PPS_OUT','2':'GND'},FP['bnc'],mfr='TE Connectivity',mpn='1-1478035-0',note='rear panel')
# Si5351C
K.add(ref('U'),'Oscillator','Si5351C-B-GM','Si5351C-B-GM',
  pins={'1':'XA_DNP','2':'XB_DNP','3':'SYN_INTR','4':'I2C0_SCL','5':'I2C0_SDA','6':'OCXO_10M_3V3','7':'AUX_OEB','10':'3V3_SYN','11':'3V3_SYN','13':'AUX_CLK0','14':'3V3_SYN','18':'3V3_SYN','20':'3V3_SYN','21':'GND'},
  nc=('8','9','12','15','16','17','19'),fp=FP['qfn20'],xy=(170,60),mfr='Skyworks',mpn='SI5351C-B-GM',note='I2C 0x60. XA/XB wired to DNP crystal Y1 only; with CLKIN used they stay open. Verify EP size.')
K.FB('3V3','3V3_SYN','BLM18PG221SN1D'); K.C('10uF 10V','3V3_SYN','GND','c8')
for _ in range(5): K.C('100nF','3V3_SYN','GND')
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
# ===================== MCU & UI =====================
M = S('MCU_UI','mcu_ui.kicad_sch', 200, 40)
M.text('MCU + UI: Waveshare RP2350-Plus module soldered via castellated pads. GPIO map = docs v0.9 (GP16 = OCXO_FLT).', 30, 14, 2.5)
M.add(ref('A'),'HamREF','RP2350-Plus','RP2350-Plus',
  pins={'1':'GNSS_RXD','2':'GNSS_TXD','4':'I2C1_SDA','5':'I2C1_SCL','6':'I2C0_SDA','7':'I2C0_SCL','9':'PPS_GNSS','10':'OCXO_10M_3V3','11':'PPS_MCU','12':'GNSS_RESET',
        '14':'GNSS_EXTINT','15':'ENC_A','16':'ENC_B','17':'ENC_SW','19':'LED_DATA_3V3','20':'AUX_OEB','21':'GP16_OCXO_FLT','27':'OCXO_EN','29':'SYN_INTR','30':'RUN_MOD',
        '31':'ADC_5V','32':'ADC_NTC','34':'ADC_EFC','36':'3V3','39':'VSYS','40':'VBUS_MOD','22':'GP17','24':'GP18','25':'GP19','26':'GP20'},
  nc=('35','37'),fp='HamREF:RP2350-Plus_Castellated',xy=(80,110),mfr='Waveshare',mpn='RP2350-Plus',note='footprint to be drawn from STEP/drawing; see docs')
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
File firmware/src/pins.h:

/* HamREF proto-v0.1 GPIO map (RP2350, Waveshare RP2350-Plus). Author: Erik, OH2LAK */
#ifndef HAMREF_PINS_H
#define HAMREF_PINS_H

#define PIN_GNSS_TX      0   /* UART0 TX -> LEA-M8S RXD */
#define PIN_GNSS_RX      1   /* UART0 RX <- LEA-M8S TXD */
#define PIN_DAC_SDA      2   /* I2C1 */
#define PIN_DAC_SCL      3
#define PIN_OLED_SDA     4   /* I2C0 */
#define PIN_OLED_SCL     5
#define PIN_PPS_IN       6   /* GNSS TIMEPULSE (1PPS)   -- must be PIN_TEN_MHZ_IN - 1 */
#define PIN_TEN_MHZ_IN   7   /* OCXO 10 MHz (squared)   -- PIO in_base = PIN_PPS_IN   */
#define PIN_PPS_OUT      8
#define PIN_GNSS_RESET_N 9
#define PIN_GNSS_EXTINT0 10
#define PIN_ENC_A        11
#define PIN_ENC_B        12
#define PIN_ENC_BTN      13
#define PIN_WS2812       14
#define PIN_OCXO_FLT     16
#define PIN_OCXO_EN      21
#define PIN_ADC_5V       26
#define PIN_ADC_NTC      27
#define PIN_ADC_EFC      28

#define DAC_I2C          i2c1
#define DAC_I2C_ADDR     0x60  /* MCP4725 A0=GND; check the schematic */
#define GNSS_UART        uart0
#define GNSS_BAUD        9600

#endif
